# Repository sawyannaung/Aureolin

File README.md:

# Aureolin
Designing a Smartwatch

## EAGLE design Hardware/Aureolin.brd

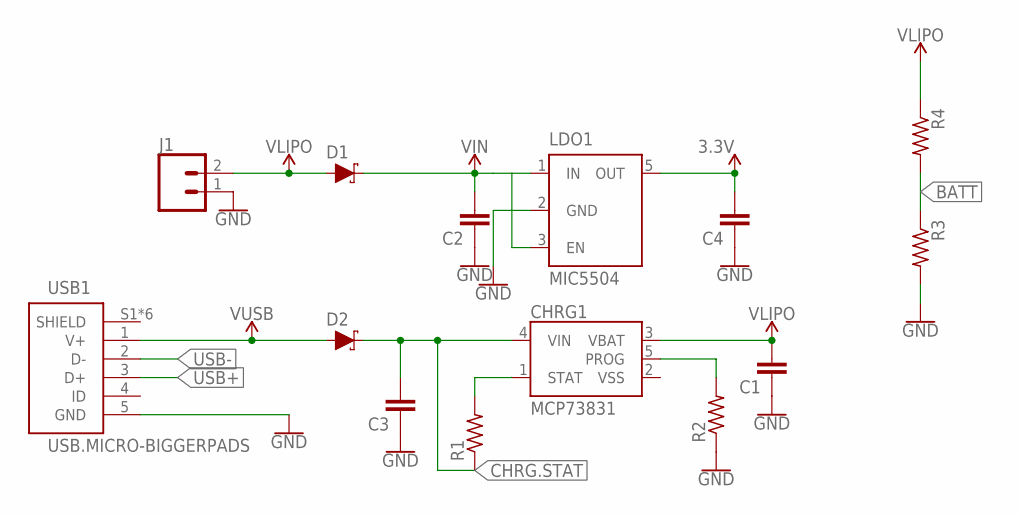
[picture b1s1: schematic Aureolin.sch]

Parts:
C1, C2, C3, C4: CAPACITOR0603; C0603
CHRG1: MCP73831; SOT23-5
D1, D2: SCHOTTKY-USC; USC
J1: CONN_02; 1X02
LDO1: MIC5504; SOT23-5
R1, R2, R3, R4: RESISTOR0603; R0603
USB1: USB.MICRO-BIGGERPADS; USB-MICRO-01.BIGGERPADS

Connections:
3.3V: C4.2, LDO1.5 (OUT)
BATT: R3.1, R4.2
CHRG.STAT: C3.2, CHRG1.4 (VIN), D2.- (C), R1.1
GND: C1.1, C2.1, C3.1, C4.1, J1.1, LDO1.2 (GND), R2.1, R3.2, USB1.5 (GND)
unnamed: CHRG1.5 (PROG), R2.2
unnamed: CHRG1.1 (STAT), R1.2
USB+: USB1.3 (D+)
USB-: USB1.2 (D-)
VIN: C2.2, D1.- (C), LDO1.1 (IN), LDO1.3 (EN)
VLIPO: C1.2, CHRG1.3 (VBAT), D1.+ (A), J1.2, R4.1
VSS: CHRG1.2 (VSS)
V_USB: D2.+ (A), USB1.1 (V+)

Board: 2 copper layers, 14 parts (0 on the bottom side), 9 nets, no tracks yet.

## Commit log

2020-02-08 Firmware uploard
2020-02-08 Hardware upload
